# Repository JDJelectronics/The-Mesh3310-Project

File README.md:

# The-Mesh3310-Project
Make the world's strongest node.

## 📱 Mesh3310: The Ultimate Off-Grid Communicator
Mesh3310 is an open-source hardware project that revives the legendary Nokia 3310 (Classic). It replaces the obsolete 2G internals with a modern, high-performance PCB.

The goal is to turn this indestructible icon into a rugged, long-range mesh networking node that runs **Meshtastic** and **MeshCore**.

## 🚀 The Vision
The Nokia 3310 is famous for its durability, tactile keypad and ergonomic design. Our custom board drops straight into the original housing and gives the phone a second life as a decentralized communicator that does not rely on cell towers or the internet. When a network *is* available, the built-in LTE modem can connect the mesh to the rest of the world.

## ⚡ Key Specifications
| Function | Part |
|---|---|
| MCU | Nordic **nRF52840** (Cortex-M4F, Bluetooth LE, USB) |
| LoRa | Semtech **SX1262** (22 dBm), 868 MHz chip antenna in the original antenna area; optional U.FL assembly variant for an external antenna |
| Cellular / GNSS | Nordic **nRF9151** (LTE-M / NB-IoT, DECT NR+, GNSS) with a SKY65723 GNSS LNA; antennas via U.FL |
| Bluetooth antenna | On-board 2.4 GHz chip antenna |
| Power | TI BQ24074 charger + TPS63031 buck-boost, original 3310 battery contacts |
| Charging / USB | Through the original bottom connector (USB data to the nRF52840) |
| Display / input | Original PCD8544 monochrome LCD, full keypad with backlight, side power button (short press to firmware, 7.5 s hardware power-off via TPS3420) |
| Audio | MAX98357A amplifier for the speaker, microphone, buzzer and vibration motor contacts |
| Storage | 2 × 16 Mbit flash (MX25R1635F), one for each Nordic chip |
| Firmware | Built to run Meshtastic and MeshCore |

## 🛠 Project Status: Rev. G – first prototypes being ordered 🏗️
- The schematic is complete and passes ERC.
- The **4-layer PCB** (1.0 mm, so it fits the original housing; JLCPCB 4-layer stackup with 3313 prepreg) is fully routed, passes DRC and matches the schematic.
- Board outline, mounting holes, battery contacts, display, SIM, speakers, keypad and backlight LEDs match the original Nokia 3310 housing.
- Controlled-impedance RF lines (50 Ω) and a solid ground plane under all three radios.
- Every assembled part has an **LCSC part number**, ready for JLCPCB assembly.

Next steps: the first 2 assembled prototypes are being ordered at JLCPCB (waiting for the nRF9151 via global sourcing). After that: tune the RF matching networks (LoRa chip antenna first) and start firmware bring-up.

| Top | Bottom (keypad side) |
|---|---|
|  |  |

## 📂 Repository Layout
| Folder | Contents |
|---|---|
| `Kicad_Mesh3310/` | KiCad 9 project (schematic, PCB, libraries, 3D models) |
| `Kicad_Mesh3310/datasheets/` | Datasheets of the main components |
| `productie/` | Gerbers, drill files, BOM and pick-and-place files, plus manufacturing notes (Dutch). Upload `Mesh3310-JLC-stuklijst.csv` and `Mesh3310-JLC-positie.csv` to JLCPCB. |
| `productie/variant-UFL/` | Assembly variant with LoRa on a U.FL connector instead of the chip antenna (same gerbers) |
| `afbeeldingen/` | Renders of the board |

## 🤝 How You Can Help
We are actively looking for contributors. Your input can directly shape the hardware.

- **Hardware engineering**: review the schematic and layout, and help with RF tuning.
- **Firmware development**: port Meshtastic/MeshCore to the legacy LCD and keypad matrix.
- **Mechanical design**: check the fit in original and replacement shells, and design internal 3D-printed parts.

## 💬 Community & Contributing
Most of the coordination happens on Discord.

Join our Discord: https://discord.gg/E6Sk9hmUE

### Concept images

## License
MIT

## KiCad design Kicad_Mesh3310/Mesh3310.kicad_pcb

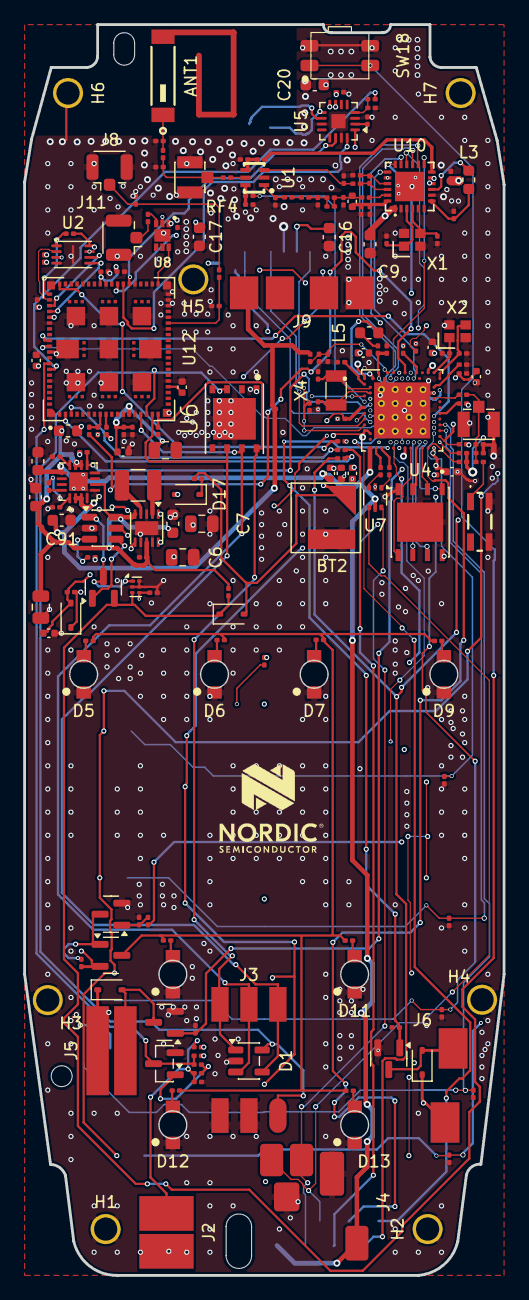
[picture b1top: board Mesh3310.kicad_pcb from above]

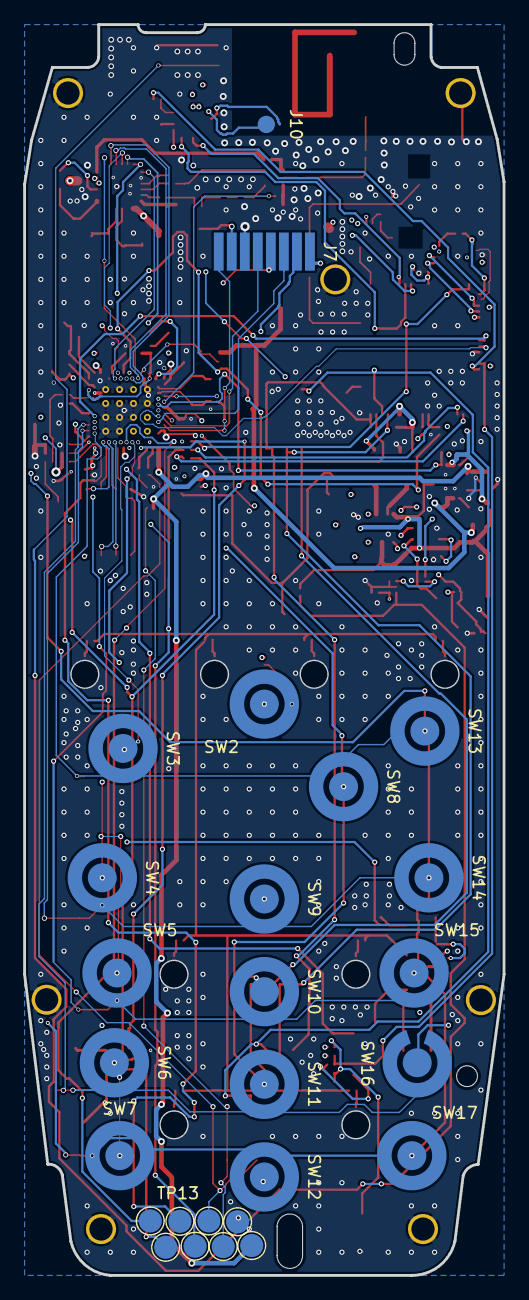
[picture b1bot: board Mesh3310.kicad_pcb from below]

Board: 4 copper layers, 41.4 x 108.0 mm, 223 parts (26 on the bottom side), 147 nets.

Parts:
ANT1: 0868AT43A0020E; XCVR_0868AT43A0020E
ANT2: 2450AT42E0100001E
BT2: ML414H-IV01E; ML414H
C1, C13, C34, C41, C48, C58, C69: 100nF; C_0201_0603Metric
C2, C4, C10, C12, C33, C43: 0.1u; C_0201_0603Metric
C3, C8: 4.7u; C_0402_1005Metric
C5, C14, C18, C21, C27, C101: 100n; C_0201_0603Metric
C6, C7: 22uF/10V; C_0805_2012Metric
C9: 1uF; C_0603_1608Metric
C11, C26: 15p; C_0201_0603Metric
C15: 33pF; C_0201_0603Metric
C16, C20, C91, C92: 10uF/10V; C_0603_1608Metric
C17: 22uF/6.3V; C_0603_1608Metric
C19: 470nF; C_0201_0603Metric
C22, C29: 15pF; C_0201_0603Metric
C28, C99: 47uF/6.3V; C_0805_2012Metric
C30: 2.0pF; C_0201_0603Metric
C31, C32: 12pF; C_0201_0603Metric
C35, C37, C39, C40, C50: 2.2uF; C_0402_1005Metric
C36, C100: 1uF; C_0402_1005Metric
C38, C76: 47nF; C_0201_0603Metric
C45, C49: 100pF; C_0201_0603Metric
C46: 820pF; C_0201_0603Metric
C47: 4.7uF; C_0402_1005Metric
C70, C71: 10pF; C_0201_0603Metric
C75, C84: 1.8pF; C_0201_0603Metric
C77: 47pF; C_0201_0603Metric
C78: 2.4pF; C_0201_0603Metric
C79, C80: NC; C_0201_0603Metric
C81: 3.3pF; C_0201_0603Metric
C82: 5.6pF; C_0201_0603Metric
C83: 39pF; C_0201_0603Metric
C85, C86: 1nF; C_0201_0603Metric
C87, C88: 3.6pF; C_0201_0603Metric
C89: 1uF/25V; C_0603_1608Metric
C90: 4.7uF/10V; C_0603_1608Metric
C93, C94: NC (afstemmen); C_0201_0603Metric
C95: 10u; C_0402_1005Metric
C96: 56pF; C_0201_0603Metric
D1: SP0504BAHT; SOT-23-5
D4, D8, D18, D20: 1N4148WS; D_SOD-323
D5, D6, D7, D9, D10, D11, D12, D13: RED; 3310_led
D17: BAT60A; D_SOD-323
FB1: 120R@100MHz 1A; L_0603_1608Metric
H1, H2, H3, H4, H5, H6, H7: 2mm_mounting_hole_sig
J2: Mic pad; 3310_mic
J3: Sim/Pad; 3310_sim
J4: Conn_01x05_Pin; 3310_dc
J5: Vibrator pad; 3310_vibrator
J6: Buzzer pad; 3310_buzzer
J7: Display; 3310_display
J8: LTE antenne: U.FL -> flexantenne (bv. Taoglas FXU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; U.FL_Hirose_U.FL-R-SMT-1_Vertical
J9: Battery; 3310_batt
J10: Speaker pad; 3310_earspeaker
J11: GNSS antenne (U.FL); U.FL_Hirose_U.FL-R-SMT-1_Vertical
L1: 3.3nH; L_0201_0603Metric
L2: 1u5; L_1210_3225Metric
L3: 15uH; L_0603_1608Metric
L4: 1.5nH; L_0201_0603Metric
L5: 10uH; L_0603_1608Metric
L6, L13: 15nH; L_0201_0603Metric
L15: 0; L_0201_0603Metric
L16: 47nH; L_0402_1005Metric
L17: 2.5nH; L_0201_0603Metric
L18: 4.7nH; L_0201_0603Metric
L19: 8.2nH; L_0201_0603Metric
NT3: NetTie_2; NetTie-2_SMD_Pad0.5mm
Q1: BC847; SOT-23
Q4, Q7: AO3400A; SOT-23
Q5, Q8: BSS138; SOT-23
Q6: IRLML6401; SOT-23
R3, R10, R28, R38, R57, R58: 0; R_0201_0603Metric
R4, R13, R29, R52: 1k; R_0201_0603Metric
R5: 1.8k; R_0201_0603Metric
R7, R11, R12, R30, R49, R50, R55: 10k; R_0201_0603Metric
R8: 33R; R_0201_0603Metric
R9: 2.2k; R_0201_0603Metric
R14, R15, R17, R20, R37, R64, R65, R66: 100k; R_0201_0603Metric
R16: 56R; R_0201_0603Metric
R18, R31, R32, R33, R34, R35: 47k; R_0201_0603Metric
R19, R21, R22, R23, R24, R25, R26, R27: 150R; R_0201_0603Metric
R36, R59, R60, R62: 1M; R_0201_0603Metric
R44, R45: 100; R_0201_0603Metric
R51: 330k; R_0201_0603Metric
R61: 0R; R_0201_0603Metric
RF3, RF4: A-IPEX1-1.25A; IPEX-SMD_3P-L2.6-W2.6-LS3.0_RF1200001R
SW2: "OK"; 3310_key
SW3, SW4, SW5, SW6, SW7, SW8, SW9, SW10, SW11, SW12, SW13, SW14, SW15, SW17: 3310_key
SW16: 3310_key_gap
SW18: POWER ON/OFF; SIDE PUSH 2.2NF 4.7x3.2x1.65mm
TP6: SWDIO; TestPoint_Pad_D2.0mm
TP7: SWO; TestPoint_Pad_D2.0mm
TP8: SWDCLK; TestPoint_Pad_D2.0mm
TP9: VBUS; TestPoint_Pad_D2.0mm
TP10: GND; TestPoint_Pad_D2.0mm
TP11: USB_D-; TestPoint_Pad_D2.0mm
TP12: USB_D+; TestPoint_Pad_D2.0mm
TP13: RESET; TestPoint_Pad_D2.0mm
U1: TPE4259-63; SOT-363-6_L2.0-W1.3-P0.65-LS2.1-BL
U2: MX25R1635FZUIH0; Winbond_USON-8-1EP_3x2mm_P0.5mm_EP0.2x1.6mm
U3: BQ24074RGT; VQFN-16-1EP_3x3mm_P0.5mm_EP1.6x1.6mm
U4: MX25R1635FZNIH0; SON127P500X600X80-9N
U5: MAX98357A; TQFN-16-1EP_3x3mm_P0.5mm_EP1.23x1.23mm
U6: SIM-ST-MFF2; PSON127P500X600X82-9N
U7: USBLC6-2P6; SOT-666
U8: SKY65723-81
U9: MAX16054; TSOT-23-6
U10: SX1262IMLTRT; QFN-24_L4.0-W4.0-P0.50-BL-EP2.6
U12: nRF9151-LAXX; XCVR_NRF9151-LACA-R7
U13: NRF52840-QIAA-R; XCVR_NRF52840-QIAA-R
U14: TPS63031DSK; WSON-10-1EP_2.5x2.5mm_P0.5mm_EP1.2x2mm
U15: TPS3420DDRYR; Texas_USON-6_1x1.45mm_P0.5mm_SMD
X1, X2: S201632M10PF10PPM 32MHz; CRYSTAL-SMD_4P-L2.0-W1.6-BL
X4: 32.768KHz; Crystal_SMD_3215-2Pin_3.2x1.5mm

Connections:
+3V3: C3.1, C6.1, C7.1, C9.1, C13.1, C17.1, C18.2, C20.2, C33.1, C34.1, C35.1, C37.1, C39.1, C40.1, C43.1, C58.1, C69.2, C101.2, D4.1 (K), D8.1 (K), D17.2 (A), J5.1, J6.1, J7.8, Q6.2 (S), R8.2, R9.2, R11.2, R18.2, R30.2, R49.2, R50.2, R66.1, U2.3, U2.7, U2.8, U4.8 (VCC), U5.7 (VDD), U5.8 (VDD), U8.1 (VCC), U10.1 (VDD_IN), U10.10 (VBAT), U10.11 (VBAT_IO), U12.65 (VDD_GPIO), U13.A22 (VDD), U13.AD14 (VDD), U13.AD23 (VDD), U13.B1 (VDD), U13.W1 (VDD), U13.Y2 (VDDH), U14.1 (VOUT), U14.10 (FB), U15.4
/GSM/COEX0: C12.1, R14.1, U8.2 (VEN), U12.52 (COEX0)
/GSM/FLASH_CS: R66.2, U2.1, U12.61 (P0.04)
/GSM/FLASH_MISO: U2.2, U12.62 (P0.05)
/GSM/FLASH_MOSI: U2.5, U12.64 (P0.07)
/GSM/FLASH_SCK: U2.6, U12.63 (P0.06)
/GSM/RF_ANT: C93.1, R61.1, U12.35 (ANT)
/GSM/RF_GPS: U8.6 (RF_OUT), U12.42 (GPS)
/GSM/RF_IN: C11.1, U8.3 (RF_IN)
/GSM/SIM_CLK: D1.4 (K), J3.3, U6.6 (CLK), U12.18 (SIM_CLK)
/GSM/SIM_IO: D1.5 (K), J3.6, U6.3 (I/O), U12.17 (SIM_IO)
/GSM/SIM_RST: D1.3 (K), J3.2, U6.7 (RST), U12.16 (SIM_RST)
/GSM/SIM_VCC: C4.1, D1.1 (K), J3.1, U6.8 (VCC), U12.19 (SIM_1V8)
/GSM/VDD_9151: C2.1, C26.1, C28.1, C95.1, FB1.2, U12.14 (VDD)
/I2S_BCLK: U5.16 (BCLK), U12.48 (P0.29)
/I2S_LRCK: U5.14 (LRCLK), U12.47 (P0.28)
/I2S_SDOUT: U5.1 (DIN), U12.49 (P0.30)
/LORA/DIO2: R45.1, U10.12 (DIO2)
/LORA/XTA: C70.1, U10.3 (XTA), X1.1
/LORA/XTB: C71.1, U10.4 (XTB), X1.3
/MCU/DCC: L5.2, U13.B3 (DCC)
/MCU/DEC1: C41.2, U13.C1 (DEC1)
/MCU/DEC2: C48.2, U13.A18 (DEC2)
/MCU/DEC3: C45.2, U13.D23 (DEC3)
/MCU/DEC4: C36.2, C38.1, C49.2, L6.1, U13.B5 (DEC4), U13.E24 (DEC6)
/MCU/DEC5: C46.2, U13.N24 (DEC5)
/MCU/DECUSB: C47.1, U13.AC5 (DECUSB)
/MCU/DIODE_USB_D+: R57.2, U7.1 (I/O1)
/MCU/DIODE_USB_D-: R58.2, U7.3 (I/O2)
/MCU/NRF_USB_D+: R57.1, U13.AD6 (D+)
/MCU/NRF_USB_D-: R58.1, U13.AD4 (D-)
/MCU/P0.06: C1.1, SW2.1, U13.L1 (P0.06)
/MCU/P0.20_QSPI_SIO_0: U4.5 (SI/SIO0), U13.AD16 (P0.20)
/MCU/P0.21_QSPI_SCK: U4.6 (SCLK), U13.AC17 (P0.21)
/MCU/P0.22_QSPI_SIO_2: U4.3 (~WP/SIO2), U13.AD18 (P0.22)
/MCU/P0.23_QSPI_SIO_3: U4.7 (~RESET/SIO3), U13.AC19 (P0.23)
/MCU/P0.24_QSPI_SIO_1: U4.2 (SO/SIO1), U13.AD20 (P0.24)
/MCU/P0.25_QSPI_CSN: U4.1 (~CS), U13.AC21 (P0.25)
/MCU/P1.00_SWO: R50.1, TP7.1, U13.AD22 (P1.00/TRACEDATA0)
/MCU_RESETn: TP13.1, U13.AC13 (P0.18/NRESET)
/MIC_OUT: Q1.3 (C), R30.1, R36.2, U12.73 (P0.13/AIN0)
/P0.02_PWR_OFF: R51.2, U9.3 (CLR), U13.A12 (P0.02/AIN0)
/P0.03_LORA_MISO: U10.16 (MISO), U13.B13 (P0.03/AIN1)
/P0.04_LORA_RF_SW1: R44.1, U13.J1 (P0.04/AIN2)
/P0.05_~CHG: R11.1, U3.9 (~CHG), U13.K2 (P0.05/AIN3)
/P0.07_DSP_D/C: J7.5, U13.M2 (P0.07/TRACECLK)
/P0.08_DSP_SCK: J7.7, U13.N1 (P0.08)
/P0.11_DSP_SDIN: J7.6, U13.T2 (P0.11/TRACEDATA2)
/P0.12_DSP_RESETn: J7.1, R65.2, U13.U1 (P0.12/TRACEDATA1)
/P0.13_BUZZ: Q7.1 (G), R20.2, U13.AD8 (P0.13)
/P0.14_VIBR: Q4.1 (G), R15.2, U13.AC9 (P0.14)
/P0.15_BACKLIGHT: R16.1, U13.AD10 (P0.15)
/P0.26_PWR_KNOP: BT2.1 (+), D18.2 (A), R52.1, U13.G1 (P0.26)
/P0.27_GSM_WAKE: R29.1, U13.H2 (P0.27)
/P0.28_LORA_BUSY: U10.14 (BUSY), U13.B11 (P0.28/AIN4)
/P0.29_LORA_DIO1: U10.13 (DIO1), U13.A10 (P0.29/AIN5)
/P0.30_LORA_RST: U10.15 (NRESET), U13.B9 (P0.30/AIN6)
/P0.31_BAT_MEAS: C27.2, R59.1, R60.2, U13.A8 (P0.31/AIN7)
/P1.07_GSM_RX: U12.69 (P0.10), U13.P23 (P1.07)
/P1.08_GSM_TX: U12.70 (P0.11), U13.P2 (P1.08)
/P1.09_DSP_CSN: J7.4, U13.R1 (P1.09/TRACEDATA3)
/P1.12_LORA_SPI_NSS: U10.19 (NSS), U13.B17 (P1.12)
/P1.13_LORA_SCK: U10.18 (SCK), U13.A16 (P1.13)
/P1.14_LORA_MOSI: U10.17 (MOSI), U13.B15 (P1.14)
/P1.15_GSM_RESET: R13.1, U13.A14 (P1.15)
/POWER/EN_3V3: C100.1, D20.2 (A), R64.2, U14.6 (EN)
/POWER/KNOP: D18.1 (K), Q8.2 (S), R62.2, SW18.1, SW18.3 (K), U15.3
/POWER/KNOP_IN: Q8.3 (D), U9.1 (IN), U15.1
/POWER/PWR_ENn: Q8.1 (G), U9.4 (~OUT)
/POWER/VBAT: C91.1, J9.1, R59.2, U3.2 (BAT), U3.3 (BAT)
/SWDCLK: R10.2, R55.2, TP8.1, U13.AA24 (SWDCLK)
/SWDIO: R28.1, R49.1, TP6.1, U13.AC24 (SWDIO)
/Shutdown_Mono: R37.1, U12.74 (P0.14/AIN1)
/USB_D+: J4.4, TP12.1, U7.6 (I/O1)
/USB_D-: J4.5, TP11.1, U7.4 (I/O2)
ANT: R3.2, U13.H23 (ANT)
GND: ANT2.3 (GND_1), ANT2.4 (GND_2), BT2.2 (-), C1.2, C2.2, C3.2, C4.2, C5.1, C6.2, C7.2, C8.2, C9.2, C10.2, C12.2, C13.2, C15.1, C16.2, C17.2, C18.1, C19.2, C20.1, C21.1, C22.2, C26.2, C27.1, C28.2, C29.2, C31.1, C32.1, C33.2, C34.2, C35.2, C36.1, C37.2, C38.2, C39.2, C40.2, C41.1, C43.2, C45.1, C46.1, C47.2, C48.1, C49.1, C50.2, C58.2, C69.1, C70.2, C71.2, C75.1, C76.2, C77.2, C79.1, C80.1, C82.2, C84.2, C85.2, C86.2, C87.2, C88.2, C89.2, C90.2, C91.2, C92.2, C93.2, C94.2, C95.2, C99.2, C100.2, C101.1, D1.2 (A), D5.1 (K), D6.1 (K), D7.1 (K), D9.1 (K), D10.1 (K), D11.1 (K), D12.1 (K), D13.1 (K), H1.1, H2.1, H3.1, H4.1, H5.1, H6.1, H7.1, J2.2, J3.4, J3.5, J4.2, J4.3, J7.3, J8.2 (Ext), J9.4, J11.2, NT3.1, Q1.2 (E), Q4.2 (S), Q5.2 (S), Q7.2 (S), R4.1, R5.1, R7.1, R14.2, R15.1, R17.1, R20.1, R31.1, R32.1, R33.1, R34.1, R35.1, R38.2, R51.1, R55.1, R60.1, R65.1, RF3.2, RF4.2, RF4.3, SW18.2, SW18.4 (A), TP10.1, U1.2 (GND), U2.4, U2.9, U3.4 (~CE), U3.5 (EN2), U3.8 (VSS), U3.17 (VSS), U4.4 (GND), U4.9 (EXP), U5.3 (GND), U5.11 (GND), U5.15 (GND), U5.17 (PAD), U6.1 (GND), U6.9 (EPAD), U7.2 (GND), U8.7 (GND), U9.2 (GND), U10.2 (GND), U10.5 (GND), U10.8 (GND), U10.20 (GND), U10.25 (GND), U12.1 (GND), U12.7 (GND), U12.13 (GND), U12.15 (GND), U12.20 (GND), U12.25 (GND), U12.30 (GND), U12.34 (GND), U12.36 (GND), U12.38 (GND), U12.39 (GND), U12.40 (GND), U12.41 (GND), U12.43 (GND), U12.46 (GND), U12.51 (GND), U12.55 (GND), U12.60 (GND), U12.66 (GND), U12.71 (GND), U12.76 (GND), U12.105 (GND), U12.106 (GND), U12.107 (GND), U12.108 (GND), U12.109 (GND), U12.110 (GND), U12.111 (GND), U12.112 (GND), U12.113 (GND), U13.74 (VSS), U13.B7 (VSS), U14.3 (PGND), U14.7 (PS/SYNC), U14.9 (GND), U14.11 (PGND), U15.2, U15.5, U15.6, X1.2 (GND), X1.4 (GND), X2.2, X2.4
unnamed: ANT1.1 (FEED), C88.1, L19.2
unnamed: ANT2.1 (FEEDING_POINT), L4.1
unnamed: C30.2, L1.2, L4.2, R3.1, RF3.1
unnamed: C80.2, C81.1, L15.2, L16.2, L17.1
unnamed: C81.2, C82.1, C83.1, L17.2
unnamed: C83.2, L18.1
unnamed: C87.1, C96.2, L19.1, RF4.1
unnamed: D4.2 (A), J5.2, Q4.3 (D)
unnamed: D5.2 (A), R19.2
unnamed: D6.2 (A), R21.2
unnamed: D7.2 (A), R22.2
unnamed: D8.2 (A), J6.2, Q7.3 (D)
unnamed: D9.2 (A), R23.2
unnamed: D10.2 (A), R24.2
unnamed: D11.2 (A), R25.2
unnamed: D12.2 (A), R26.2
unnamed: D13.2 (A), R27.2
unnamed: D17.1 (K), R52.2
unnamed: C14.1, C15.2, J2.1, R9.1
unnamed: C16.1, J7.2
unnamed: C94.1, J8.1 (In), R61.2
unnamed: J10.1, U5.9 (OUTP)
unnamed: J10.2, U5.10 (OUTN)
unnamed: C11.2, J11.1
unnamed: L5.1, L6.2
unnamed: C14.2, Q1.1 (B), R36.1
unnamed: Q5.3 (D), Q6.1 (G), R18.1
unnamed: Q5.1 (G), R16.2, R17.2
unnamed: Q6.3 (D), R19.1, R21.1, R22.1, R23.1, R24.1, R25.1, R26.1, R27.1
unnamed: R8.1, SW2.2
unnamed: C78.1, C79.2, U1.3 (RF1)
unnamed: C84.1, L18.2, U1.1 (RF2)
unnamed: C96.1, U1.5 (RFC)
unnamed: C86.1, R45.2, U1.4 (VC1)
unnamed: C85.1, R44.2, U1.6 (VC2)
unnamed: R4.2, U3.12 (ILIM)
unnamed: R5.2, U3.16 (ISET)
unnamed: R7.2, U3.1 (TS)
unnamed: R38.1, U5.2 (GAIN_SLOT)
unnamed: C21.2, R37.2, U5.4 (~SD_MODE)
unnamed: L3.2, U10.9 (DCC_SW)
unnamed: C78.2, L13.2, U10.22 (RFI_N)
unnamed: C75.2, L13.1, U10.21 (RFI_P)
unnamed: L15.1, U10.23 (RFO)
unnamed: C19.1, L3.1, U10.7 (VREG)
unnamed: C76.1, C77.1, L16.1, U10.24 (VR_PA)
unnamed: C8.1, U12.24 (DEC0)
unnamed: R12.2, U12.10 (ENABLE)
unnamed: R29.2, U12.59 (P0.03)
unnamed: R10.1, U12.3 (SWDCLK)
unnamed: R28.2, U12.4 (SWDIO)
unnamed: C10.1, R13.2, U12.9 (~RESET)
unnamed: L2.1, U14.4 (L1)
unnamed: L2.2, U14.2 (L2)
P0.16_COL_1: SW3.1, SW4.1, SW5.1, SW6.1, SW7.1, U13.AC11 (P0.16)
P0.17_COL_2: SW8.1, SW9.1, SW10.1, SW11.1, SW12.1, U13.AD12 (P0.17)
P0.19_COL_3: SW13.1, SW14.1, SW15.1, SW16.1, SW17.1, U13.AC15 (P0.19)
P1.01_ROW_1: R31.2, SW3.2, SW8.2, SW13.2, U13.Y23 (P1.01)
P1.02_ROW_2: R32.2, SW4.2, SW9.2, SW14.2, U13.W24 (P1.02)
P1.03_ROW_3: R33.2, SW5.2, SW10.2, SW15.2, U13.V23 (P1.03)
P1.04_ROW_4: R34.2, SW6.2, SW11.2, SW16.2, U13.U24 (P1.04)
P1.05_ROW_5: R35.2, SW7.2, SW12.2, SW17.2, U13.T23 (P1.05)
PWR_EN: D20.1 (K), R12.1, R64.1, U9.5 (OUT)
VBUS: C50.1, C89.1, J4.1, TP9.1, U3.13 (IN), U7.5 (VBUS), U13.AD2 (VBUS)
VSS_PA: C30.1, L1.1, NT3.2, RF3.3, U13.F23 (VSS_PA)
VSYS: C5.2, C90.1, C92.1, C99.1, FB1.1, R62.1, U3.6 (EN1), U3.10 (OUT), U3.11 (OUT), U9.6 (VCC), U14.5 (VIN), U14.8 (VINA)
XC1: C22.1, U13.B24 (XC1), X2.3
XC2: C29.1, U13.A23 (XC2), X2.1
XL1: C31.2, U13.D2 (P0.00/XL1), X4.1
XL2: C32.2, U13.F2 (P0.01/XL2), X4.2

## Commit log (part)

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2026-01-22 Update README.md
    Update REAME
2026-01-23 First commit
    First commit, Libs are still a mess
2026-01-26 Adding testpoints
    Test pint on usb and SWD debug
2026-01-27 component placing
    component placing
2026-01-27 Battery ic changes
    form Max1555 to BQ24074
2026-01-28 Cleaning and placing
    Cleaning and placing components
2026-01-30 Start of routing
    Component placing and start off routing
2026-01-30 Update README.md
    Lora module update
2026-01-31 backup work
2026-02-01 RF designing
2026-02-02 cleanup
    schematic cleanup
2026-02-03 Change antenna BT
    BT change
2026-02-04 Lora changes
    Schematic changes to from RA to SOC
2026-02-04 Lora placement
2026-02-05 Lora antenna replacement
    Lora antenna replacement, added Nordic nRF 9151 for GPS , VoIP ,VoLTE-m , SIP
2026-02-11 Backing up work
    Backup work for today
2026-02-23 Backup work
    Adding some extra pads
2026-02-23 shematic changes
    small changes in NRF component
2026-02-24 Schematic changes
    Adding gsm module , interfaces : mic+earspeaker
